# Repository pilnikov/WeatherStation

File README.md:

# WeatherStations

Проект метеостанции на ESP8266/32 (среда - Arduino IDE 1.8.5)

Поддерживаются:

Дисплеи на 7ми и 14ти сегментных индикаторах с драйверами на TM1637, HT16K33, MAX7219 (4/8 Знакомест).

LCD16х2 дисплей со встроеным знакогенератором кириллицы, интерфейс  I2C.

Матричные дисплеи на:
        
        MAX7219 8х32 и 16х32 пикселей.
        отдельном контроллере MEGA2560, 16х32 пикселей, полный цвет, интерфейс HUB75
        в версии ЕСП32, 64х64 пикселей, полный цвет, интерфейс HUB75 
        Holtek HT1632, 16х32 пикселей, 3 цвета (R, G, Orange) от Sure Electronics

Модули RTC на DS1307, DS1302, DS3231.

Управление яркостью дисплеев посредством датчика освещенности ВН1750 или фоторезистора.

Погодные датчики DHT22, Si7021, BME(/P)085/180/280, AM2320, вcтроеный в DS3231 датчик температуры.

Обмен данными между 2мя и более устройствами внутри сети посредством JSON запросов и через облачный сервис ThingSpeak.

Клиент/серверная архитектура.

Возможность работы в режиме "WiFi датчик".

Прогноз погоды с GisMeteo и OpenWeatherMap.

Синхронизация времени с NTP.

6 многофункциональных будильников с 15ю мелодиями.

Настойка через веб интерфейс.

Обновление по OTA, mdns.

Новости с newsapi.

Конфигурирование GPIO.

Дауншифтовая версия на MEGA2560 без возможности перенастройки, без прогноза, без новостей.

Немного мультиков
https://yadi.sk/i/UXBMaSDD3HfCZC

https://yadi.sk/i/Ew0egvWq3Hg48u

https://yadi.sk/i/os1wRLuz3Hg493

https://yadi.sk/i/jCs5TbVB3aA5pw теперь только один мк, безо всяких мег

https://youtu.be/F3vVPQLzyJk версия с новостями, там же есть ссылки на фото платы

Cхемы в папочке extras, там же и инфа для изготовления печатных плат.

Файлы из папки Data необходимо залить на LittleFS плагином (лежат в  папке dop).

По умолчанию первый раз запускается точка доступа с именем  Web_Clock и паролем 12345678 (задается в файле config.json из папки data перед загрузкой в LittleFS строкой  "ap_ssid":"Web_Clock","ap_pass":"12345678").Веб интерфейс будет доступен по адресу 192.168.4.1.

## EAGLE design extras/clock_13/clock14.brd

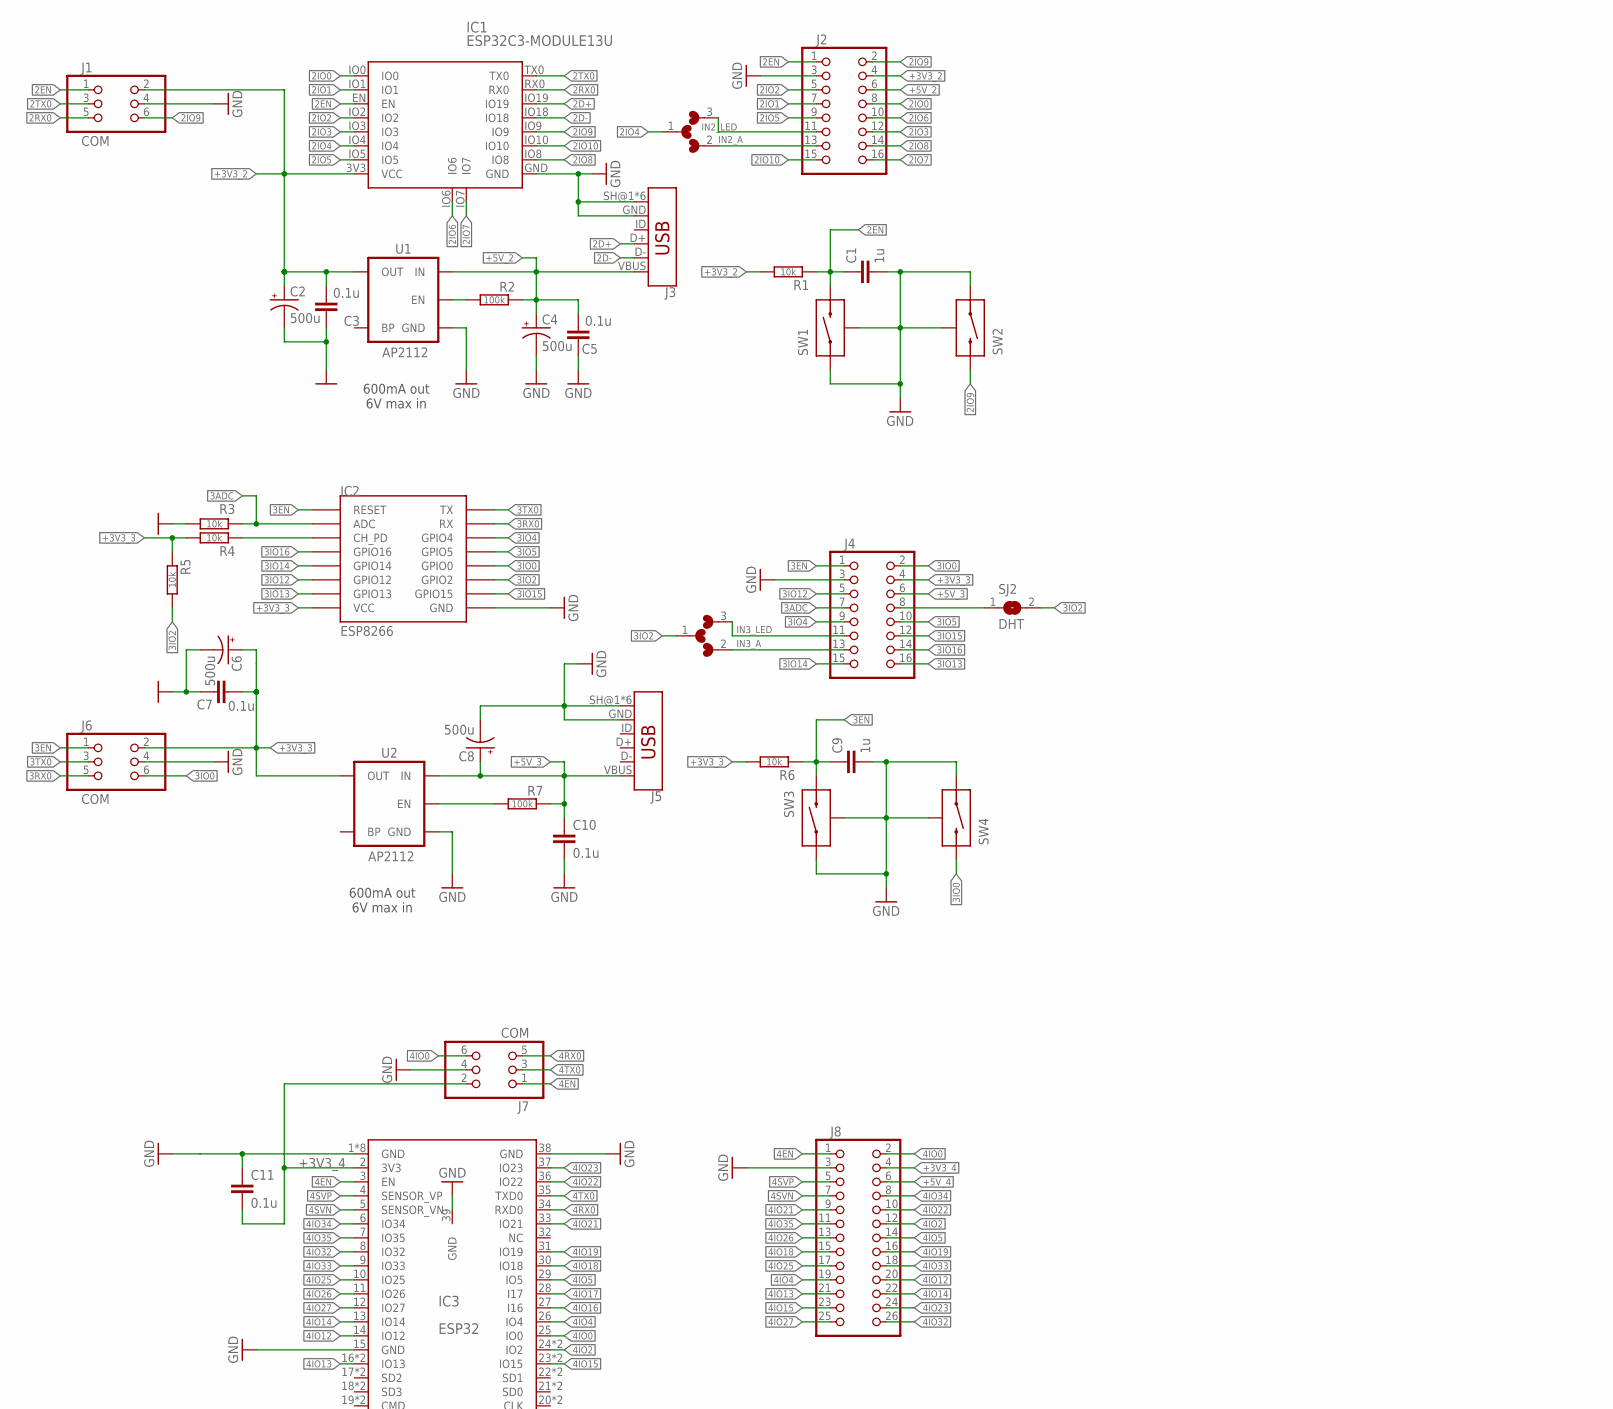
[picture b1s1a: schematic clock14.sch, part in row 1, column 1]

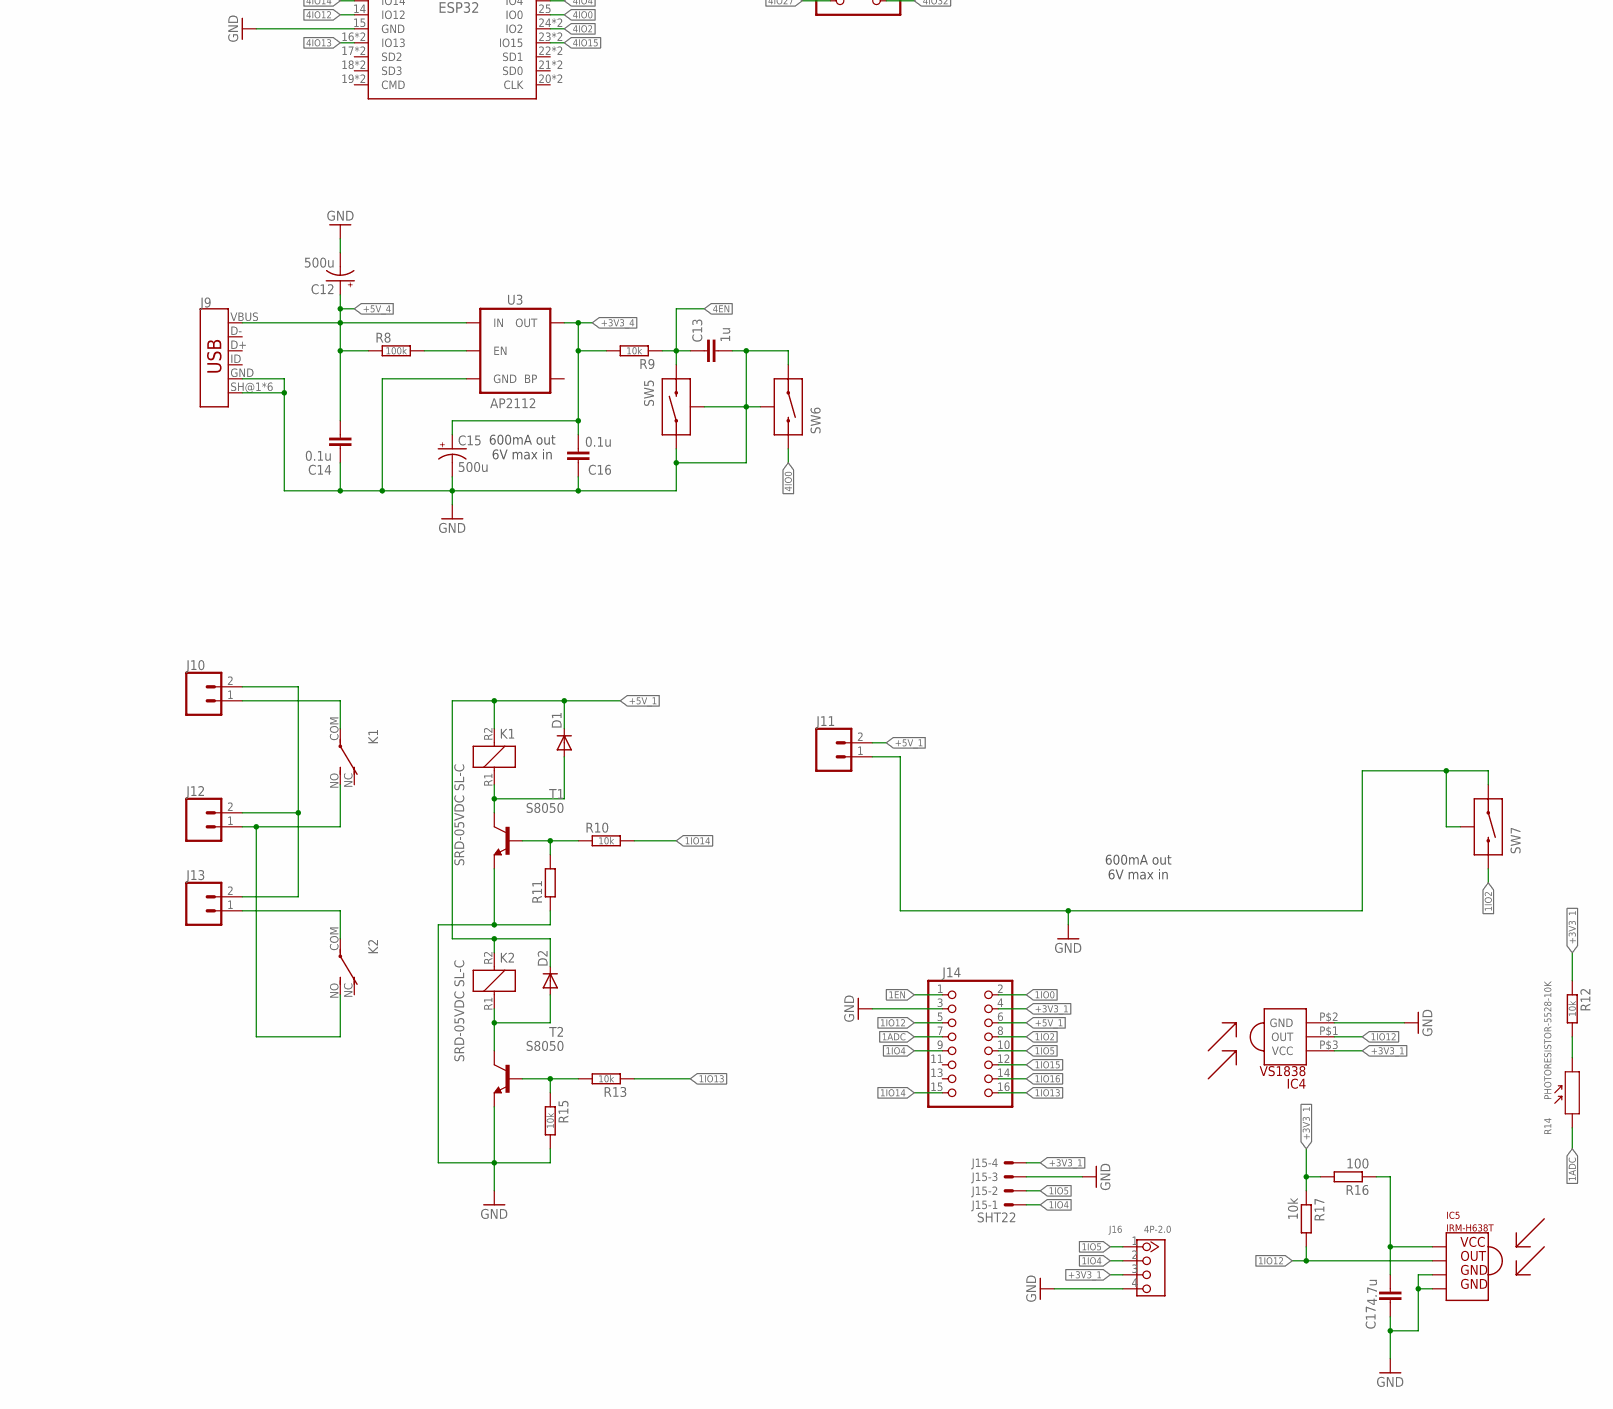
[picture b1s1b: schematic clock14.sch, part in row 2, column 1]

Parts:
C1, C9, C13: 1u; 0603-CAP
C2, C4, C6, C8, C12, C15: 500u; CPOL-RADIAL-100UF-25V
C3, C5, C7, C10, C11, C14, C16: 0.1u; 0603-CAP
C17: 4.7u; 0603-CAP
D1, D2: DIODE-SOD123; SOD123
IC1: ESP32C3-MODULE13U; ESP32C3-13U
IC2: ESP8266; ESP12-SMD
IC3: ESP32; ESP32-WROOVER/WROOM
IC4: VS1838; IR
IC5: IRM-H638T
J1, J6, J7: COM; 2X03_SMT
J2, J4, J14: HEADER-2X8; 2X8
J3, J5, J9: USB_MICRO-BFEMALE_SMT_; USB-B-MICRO-SMD_MY
J8: HEADER-2X13; 2X13
J10, J11, J12, J13: CONN_02; 1X02
J15: SHT22; 70543-04
J16: 4P-2.0; HW4-2.0
K1, K2: SRD-05VDC SL-C; SL-C
R1, R3, R4, R5, R6, R9, R10, R12, R13, R15, R17: 10k; R0603
R2, R7, R8: 100k; R0603
R11: R-EU_R0603; R0603
R14: PHOTORESISTOR-5528-10K; SNR2-3.0
R16: 100; R0603
SJ1, SJ3: L/W; MICROBUILDER_SOLDERJUMPER_ARROW_NOPASTE_3
SJ2: DHT; MICROBUILDER_SOLDERJUMPER_ARROW_NOPASTE
SW1, SW3, SW5: RST; MICROPUSH-BUT_TOP
SW2, SW4, SW6, SW7: PRG; MICROPUSH-BUT_TOP
T1, T2: S8050; SOT23-EBC
U1, U2, U3: AP2112; SOT23-5

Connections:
1ADC: J14.7, R14.1
1EN: J14.1
1EN_P: R8.2, U3.3 (EN)
1IO0: J14.2
1IO2: J14.8, SW7.B
1IO4: J14.9, J15.1, J16.2
1IO5: J14.10, J15.2, J16.1
1IO12: IC4.P$1 (OUT), IC5.OUT, J14.5, R17.2
1IO13: J14.16, R13.1
1IO14: J14.15, R10.2
1IO15: J14.12
1IO16: J14.14
2D+: IC1.IO19, J3.D+
2D-: IC1.IO18, J3.D-
2EN: C1.1, IC1.EN, J1.1, J2.1, R1.1, SW1.B
2EN_P: R2.2, U1.3 (EN)
2IO0: IC1.IO0, J2.8
2IO1: IC1.IO1, J2.7
2IO2: IC1.IO2, J2.5
2IO3: IC1.IO3, J2.12
2IO4: IC1.IO4, SJ1.1
2IO5: IC1.IO5, J2.9
2IO6: IC1.IO6, J2.10
2IO7: IC1.IO7, J2.16
2IO8: IC1.IO8, J2.14
2IO9: IC1.IO9, J1.6, J2.2, SW2.B
2IO10: IC1.IO10, J2.15
2RX0: IC1.RX0, J1.5
2TX0: IC1.TX0, J1.3
3ADC: IC2.ADC, J4.7, R3.1
3EN: C9.1, IC2.RESET, J4.1, J6.1, R6.1, SW3.B
3EN_P: R7.2, U2.3 (EN)
3IO0: IC2.GPIO0, J4.2, J6.6, SW4.B
3IO2: IC2.GPIO2, R5.2, SJ2.2, SJ3.1
3IO4: IC2.GPIO4, J4.9
3IO5: IC2.GPIO5, J4.10
3IO12: IC2.GPIO12, J4.5
3IO13: IC2.GPIO13, J4.16
3IO14: IC2.GPIO14, J4.15
3IO15: IC2.GPIO15, J4.12
3IO16: IC2.GPIO16, J4.14
3RX0: IC2.RXD0 (RX), J6.5
3TX0: IC2.TXD0 (TX), J6.3
4EN: C13.1, IC3.3 (EN), J7.1, J8.1, R9.1, SW5.B
4IO0: IC3.25 (IO0), J7.6, J8.2, SW6.B
4IO2: IC3.24 (IO2), IC3.48 (IO2), J8.12
4IO4: IC3.26 (IO4), J8.19
4IO5: IC3.29 (IO5), J8.14
4IO12: IC3.14 (IO12), J8.20
4IO13: IC3.16 (IO13), IC3.40 (IO13), J8.21
4IO14: IC3.13 (IO14), J8.22
4IO15: IC3.23 (IO15), IC3.47 (IO15), J8.23
4IO16: IC3.27 (I16)
4IO17: IC3.28 (I17)
4IO18: IC3.30 (IO18), J8.15
4IO19: IC3.31 (IO19), J8.16
4IO21: IC3.33 (IO21), J8.9
4IO22: IC3.36 (IO22), J8.10
4IO23: IC3.37 (IO23), J8.24
4IO25: IC3.10 (IO25), J8.17
4IO26: IC3.11 (IO26), J8.13
4IO27: IC3.12 (IO27), J8.25
4IO32: IC3.8 (IO32), J8.26
4IO33: IC3.9 (IO33), J8.18
4IO34: IC3.6 (IO34), J8.8
4IO35: IC3.7 (IO35), J8.11
4RX0: IC3.34 (RXD0), J7.5
4SVN: IC3.5 (SENSOR_VN), J8.7
4SVP: IC3.4 (SENSOR_VP), J8.5
4TX0: IC3.35 (TXD0), J7.3
+3V3_1: IC4.P$3 (VCC), J14.4, J15.4, J16.3, R12.1, R16.2, R17.1
+3V3_2: C2.1 (+), C3.2, IC1.3V3 (VCC), J1.2, J2.4, R1.2, U1.5 (OUT)
+3V3_3: C6.1 (+), C7.2, IC2.VCC, J4.4, J6.2, R4.2, R5.1, R6.2, U2.5 (OUT)
+3V3_4: C11.2, C15.1 (+), C16.2, IC3.2 (3V3), J7.2, J8.4, R9.2, U3.5 (OUT)
+5V_1: D1.C, D2.C, J11.2, J14.6, K1.R2 (2), K2.R2 (2)
+5V_2: C4.1 (+), C5.2, J2.6, J3.VBUS, R2.1, U1.1 (IN)
+5V_3: C8.1 (+), C10.1, J4.6, J5.VBUS, R7.1, U2.1 (IN)
+5V_4: C12.1 (+), C14.1, J8.6, J9.VBUS, R8.1, U3.1 (IN)
GND: C1.2, C2.2 (-), C3.1, C4.2 (-), C5.1, C6.2 (-), C7.1, C8.2 (-), C9.2, C10.2, C11.1, C12.2 (-), C13.2, C14.2, C15.2 (-), C16.1, C17.2, IC1.GND, IC2.GND, IC3.1 (GND), IC3.15 (GND), IC3.38 (GND), IC3.39 (GND), IC3.GND, IC3.PAD$1 (GND), IC3.PAD$4 (GND), IC3.PAD$5 (GND), IC3.PAD$7 (GND), IC3.PAD$8 (GND), IC3.PAD$9 (GND), IC4.P$2 (GND), IC5.GND, IC5.GND1, J1.4, J2.3, J3.GND, J3.SH@1 (SHIELD), J3.SH@2 (SHIELD), J3.SH@3 (SHIELD), J3.SH@4 (SHIELD), J3.SH@5 (SHIELD), J3.SH@6 (SHIELD), J4.3, J5.GND, J5.SH@1 (SHIELD), J5.SH@2 (SHIELD), J5.SH@3 (SHIELD), J5.SH@4 (SHIELD), J5.SH@5 (SHIELD), J5.SH@6 (SHIELD), J6.4, J7.4, J8.3, J9.GND, J9.SH@1 (SHIELD), J9.SH@2 (SHIELD), J9.SH@3 (SHIELD), J9.SH@4 (SHIELD), J9.SH@5 (SHIELD), J9.SH@6 (SHIELD), J11.1, J14.3, J15.3, J16.4, R3.2, R11.1, R15.2, SW1.A, SW1.SH0 (SH), SW2.A, SW2.SH0 (SH), SW3.A, SW3.SH0 (SH), SW4.A, SW4.SH0 (SH), SW5.A, SW5.SH0 (SH), SW6.A, SW6.SH0 (SH), SW7.A, SW7.SH0 (SH), T1.E, T2.E, U1.2 (GND), U2.2 (GND), U3.2 (GND)
IN2_A: J2.13, SJ1.2
IN2_LED: J2.11, SJ1.3
IN3_A: J4.13, SJ3.2
IN3_DHT: J4.8, SJ2.1
IN3_LED: J4.11, SJ3.3
IN_L: J12.1, K1.NO, K2.NO
N: J10.2, J12.2, J13.2
unnamed: IC2.CH_PD, R4.1
unnamed: D1.A, K1.R1 (1), T1.C
unnamed: R10.1, R11.2, T1.B
unnamed: D2.A, K2.R1 (1), T2.C
unnamed: R13.2, R15.1, T2.B
unnamed: R12.2, R14.2
unnamed: C17.1, IC5.VCC, R16.1
OUT_L1: J10.1, K1.COM
OUT_L2: J13.1, K2.COM

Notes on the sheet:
600mA out 6V max in

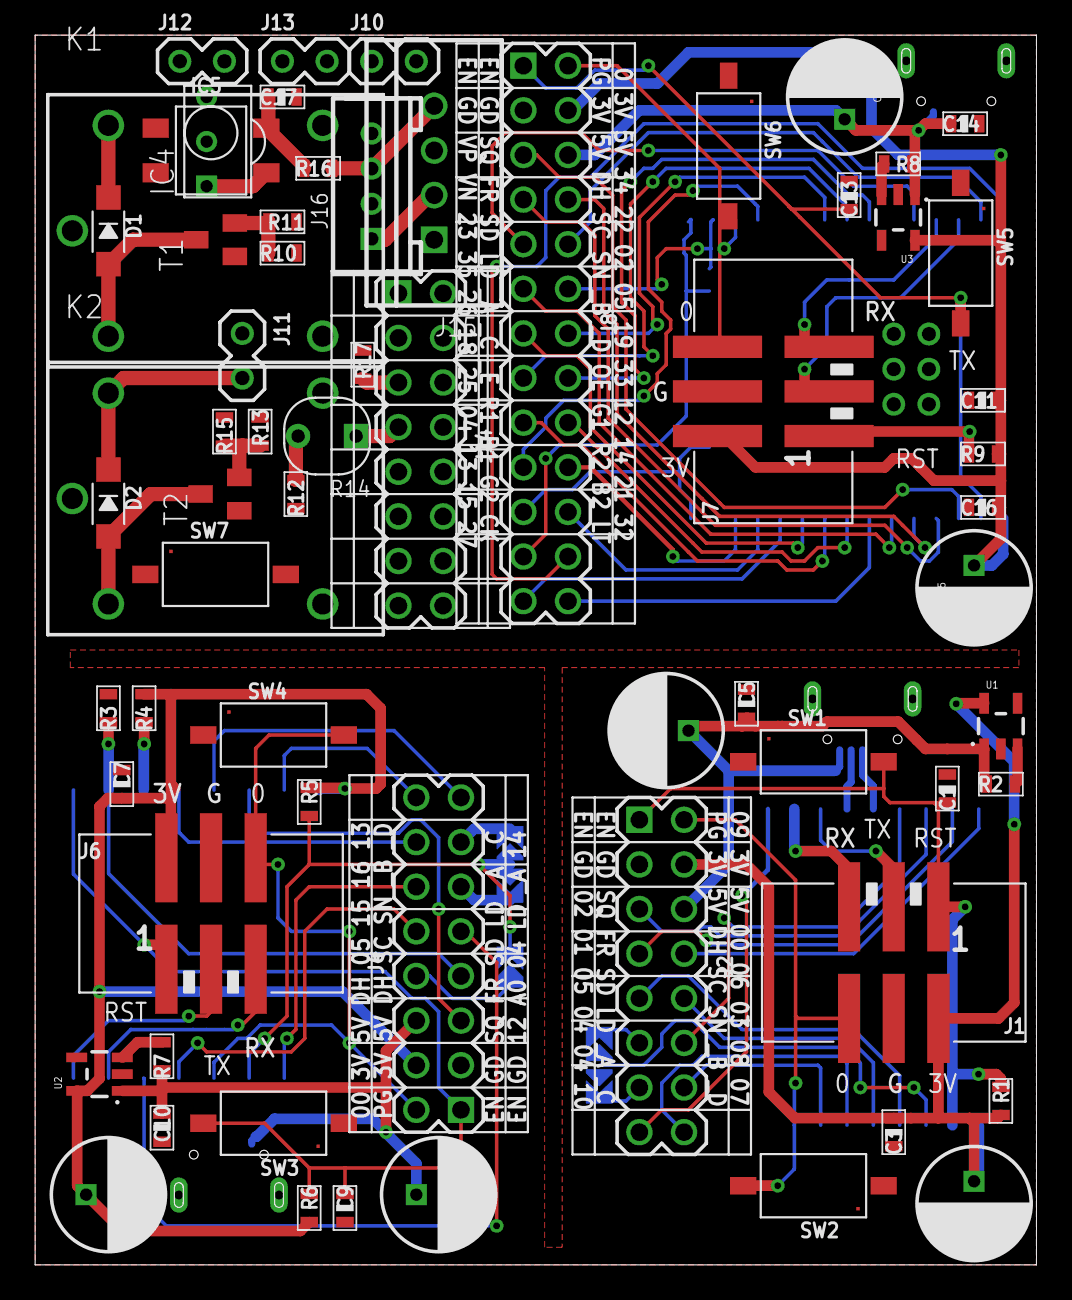
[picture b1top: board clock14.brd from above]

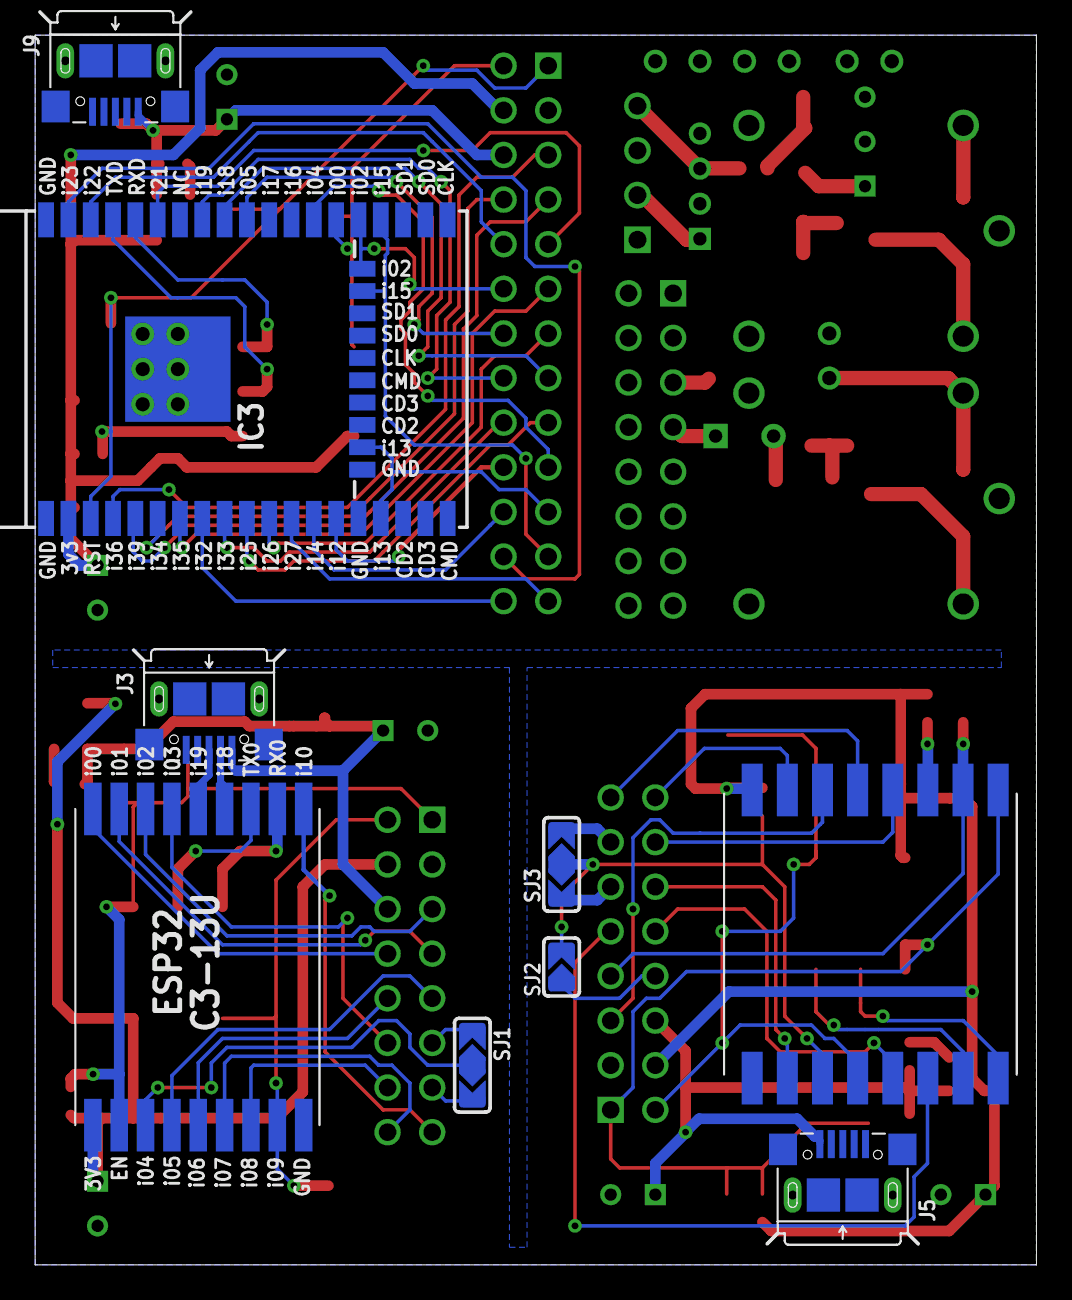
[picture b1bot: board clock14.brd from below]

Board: 2 copper layers, 57.0 x 70.0 mm, 74 parts (9 on the bottom side), 89 nets.

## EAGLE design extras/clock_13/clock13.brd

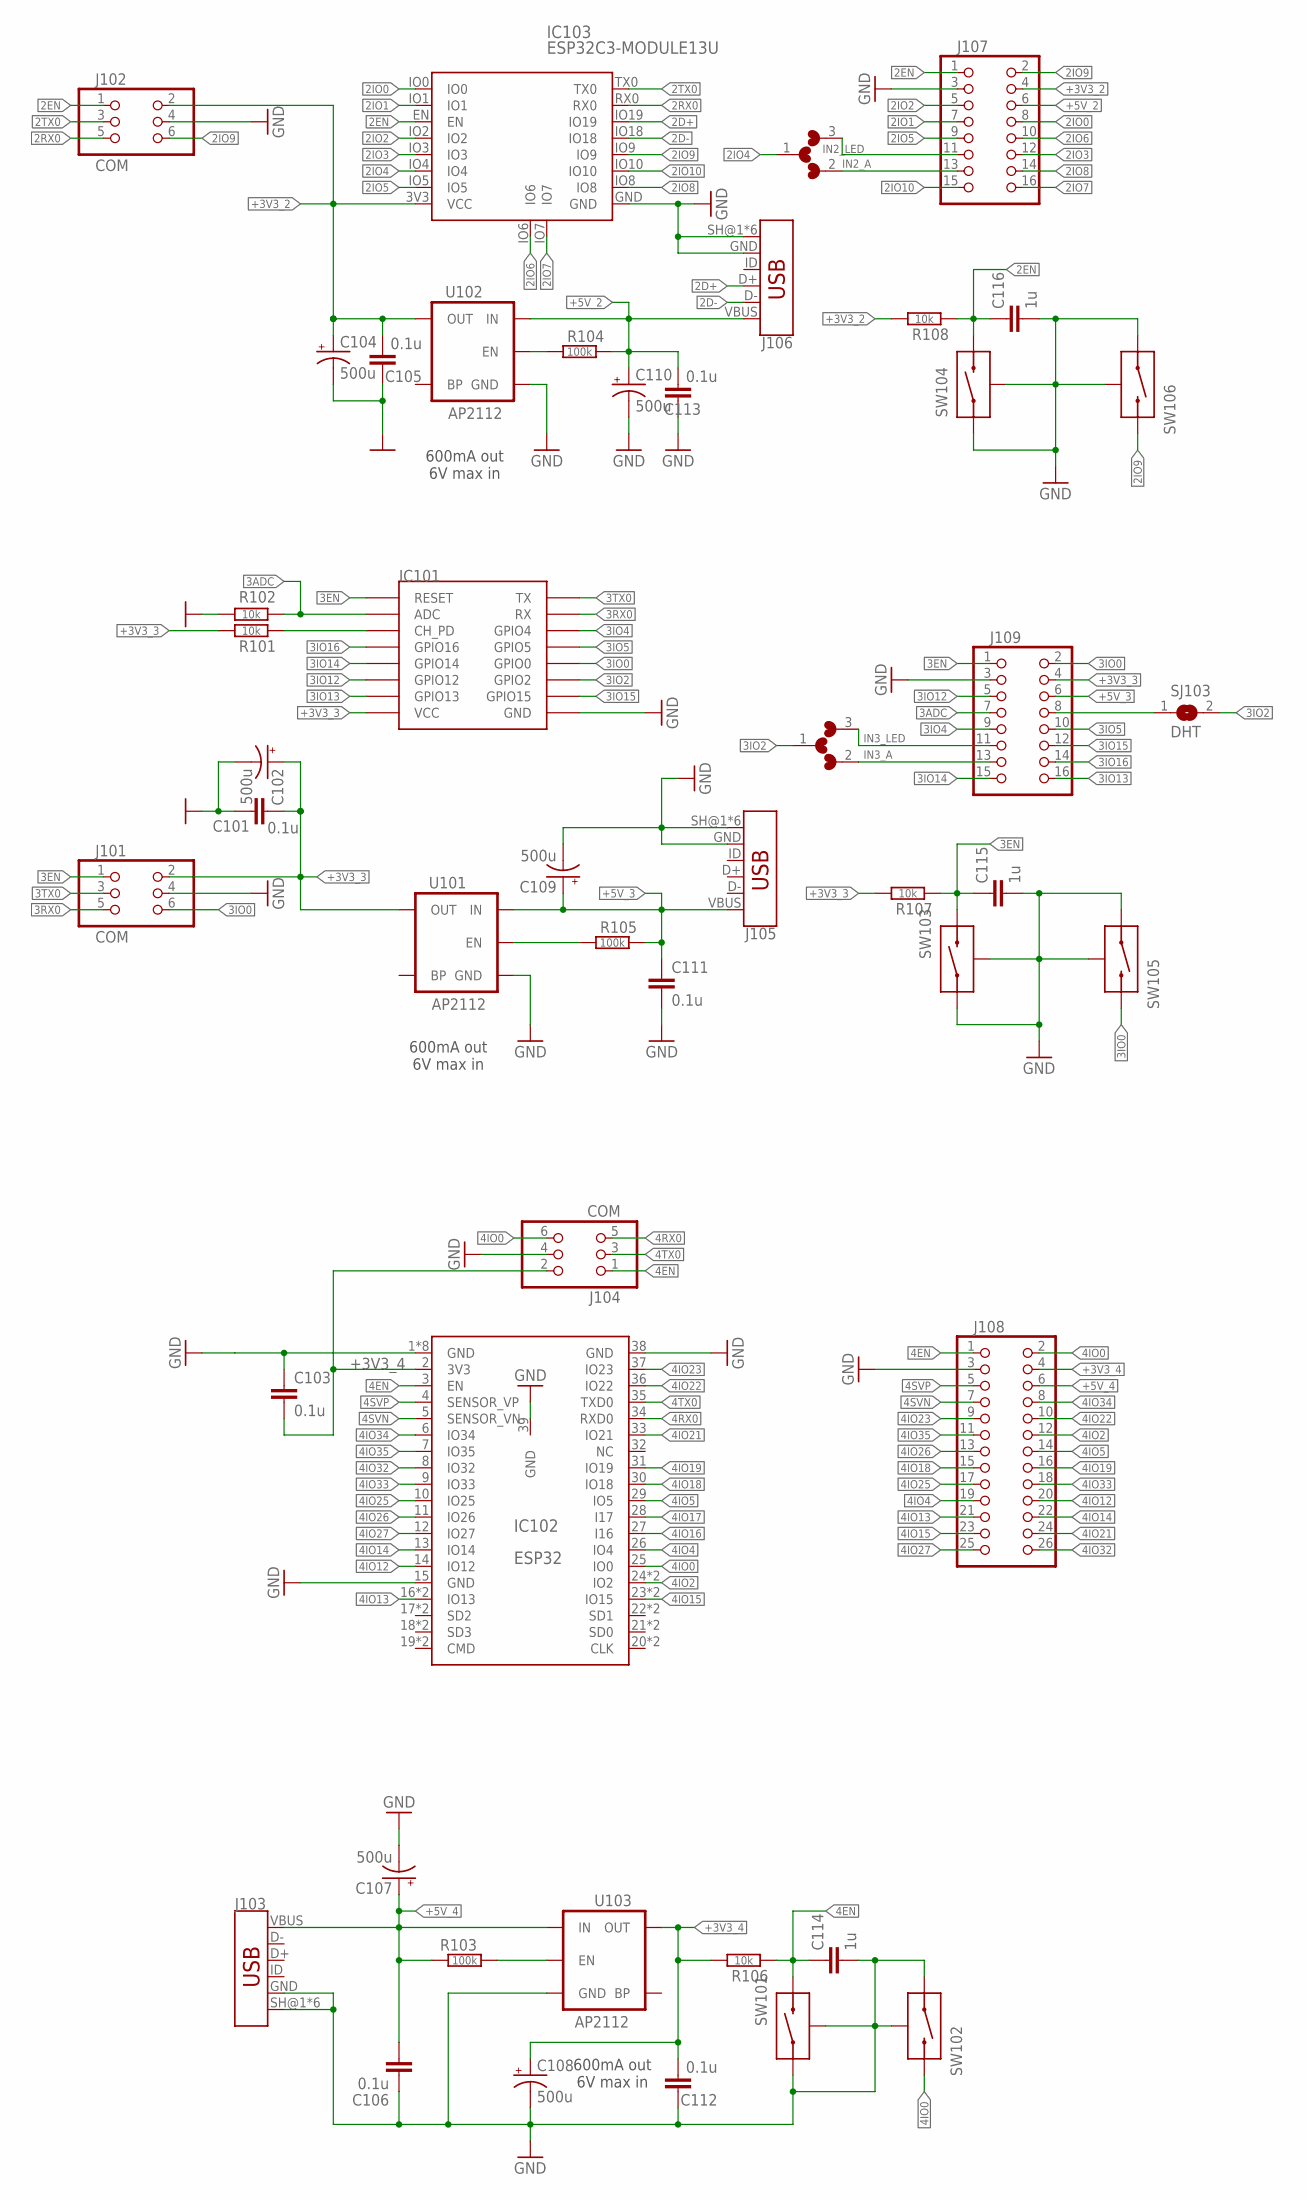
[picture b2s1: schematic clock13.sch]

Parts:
C101, C103, C105, C106, C111, C112, C113: 0.1u; 0603-CAP
C102, C104, C107, C108, C109, C110: 500u; CPOL-RADIAL-100UF-25V
C114, C115, C116: 1u; 0603-CAP
IC101: ESP12SMD; ESP12-SMD
IC102: ESP32; ESP32-WROOVER/WROOM
IC103: ESP32C3-MODULE13U; ESP32C3-13U
J101, J102, J104: COM; 2X03_SMT
J103, J105, J106: USB_MICRO-BFEMALE_SMT_; USB-B-MICRO-SMD_MY
J107, J109: HEADER-2X8; 2X8
J108: HEADER-2X13; 2X13
R101, R102, R106, R107, R108: 10k; R0603
R103, R104, R105: 100k; R0603
SJ101, SJ102: L/W; MICROBUILDER_SOLDERJUMPER_ARROW_NOPASTE_3
SJ103: DHT; MICROBUILDER_SOLDERJUMPER_ARROW_NOPASTE
SW101, SW103, SW104: RST; MICROPUSH-BUT_TOP
SW102, SW105, SW106: PRG; MICROPUSH-BUT_TOP
U101, U102, U103: AP2112; SOT23-5

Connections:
1EN_P: R103.2, U103.3 (EN)
2D+: IC103.IO19, J106.D+
2D-: IC103.IO18, J106.D-
2EN: C116.1, IC103.EN, J102.1, J107.1, R108.1, SW104.B
2EN_P: R104.2, U102.3 (EN)
2IO0: IC103.IO0, J107.8
2IO1: IC103.IO1, J107.7
2IO2: IC103.IO2, J107.5
2IO3: IC103.IO3, J107.12
2IO4: IC103.IO4, SJ101.1
2IO5: IC103.IO5, J107.9
2IO6: IC103.IO6, J107.10
2IO7: IC103.IO7, J107.16
2IO8: IC103.IO8, J107.14
2IO9: IC103.IO9, J102.6, J107.2, SW106.B
2IO10: IC103.IO10, J107.15
2RX0: IC103.RX0, J102.5
2TX0: IC103.TX0, J102.3
3ADC: IC101.ADC, J109.7, R102.1
3EN: C115.1, IC101.RESET, J101.1, J109.1, R107.1, SW103.B
3EN_P: R105.2, U101.3 (EN)
3IO0: IC101.GPIO0, J101.6, J109.2, SW105.B
3IO2: IC101.GPIO2, SJ102.1, SJ103.2
3IO4: IC101.GPIO4, J109.9
3IO5: IC101.GPIO5, J109.10
3IO12: IC101.GPIO12, J109.5
3IO13: IC101.GPIO13, J109.16
3IO14: IC101.GPIO14, J109.15
3IO15: IC101.GPIO15, J109.12
3IO16: IC101.GPIO16, J109.14
3RX0: IC101.RXD0 (RX), J101.5
3TX0: IC101.TXD0 (TX), J101.3
4EN: C114.1, IC102.3 (EN), J104.1, J108.1, R106.1, SW101.B
4IO0: IC102.25 (IO0), J104.6, J108.2, SW102.B
4IO2: IC102.24 (IO2), IC102.48 (IO2), J108.12
4IO4: IC102.26 (IO4), J108.19
4IO5: IC102.29 (IO5), J108.14
4IO12: IC102.14 (IO12), J108.20
4IO13: IC102.16 (IO13), IC102.40 (IO13), J108.21
4IO14: IC102.13 (IO14), J108.22
4IO15: IC102.23 (IO15), IC102.47 (IO15), J108.23
4IO16: IC102.27 (I16)
4IO17: IC102.28 (I17)
4IO18: IC102.30 (IO18), J108.15
4IO19: IC102.31 (IO19), J108.16
4IO21: IC102.33 (IO21), J108.24
4IO22: IC102.36 (IO22), J108.10
4IO23: IC102.37 (IO23), J108.9
4IO25: IC102.10 (IO25), J108.17
4IO26: IC102.11 (IO26), J108.13
4IO27: IC102.12 (IO27), J108.25
4IO32: IC102.8 (IO32), J108.26
4IO33: IC102.9 (IO33), J108.18
4IO34: IC102.6 (IO34), J108.8
4IO35: IC102.7 (IO35), J108.11
4RX0: IC102.34 (RXD0), J104.5
4SVN: IC102.5 (SENSOR_VN), J108.7
4SVP: IC102.4 (SENSOR_VP), J108.5
4TX0: IC102.35 (TXD0), J104.3
+3V3_2: C104.1 (+), C105.2, IC103.3V3 (VCC), J102.2, J107.4, R108.2, U102.5 (OUT)
+3V3_3: C101.2, C102.1 (+), IC101.VCC, J101.2, J109.4, R101.2, R107.2, U101.5 (OUT)
+3V3_4: C103.2, C108.1 (+), C112.2, IC102.2 (3V3), J104.2, J108.4, R106.2, U103.5 (OUT)
+5V_2: C110.1 (+), C113.2, J106.VBUS, J107.6, R104.1, U102.1 (IN)
+5V_3: C109.1 (+), C111.1, J105.VBUS, J109.6, R105.1, U101.1 (IN)
+5V_4: C106.1, C107.1 (+), J103.VBUS, J108.6, R103.1, U103.1 (IN)
GND: C101.1, C102.2 (-), C103.1, C104.2 (-), C105.1, C106.2, C107.2 (-), C108.2 (-), C109.2 (-), C110.2 (-), C111.2, C112.1, C113.1, C114.2, C115.2, C116.2, IC101.GND, IC102.1 (GND), IC102.15 (GND), IC102.38 (GND), IC102.39 (GND), IC102.GND, IC102.PAD$1 (GND), IC102.PAD$4 (GND), IC102.PAD$5 (GND), IC102.PAD$7 (GND), IC102.PAD$8 (GND), IC102.PAD$9 (GND), IC103.GND, J101.4, J102.4, J103.GND, J103.SH@1 (SHIELD), J103.SH@2 (SHIELD), J103.SH@3 (SHIELD), J103.SH@4 (SHIELD), J103.SH@5 (SHIELD), J103.SH@6 (SHIELD), J104.4, J105.GND, J105.SH@1 (SHIELD), J105.SH@2 (SHIELD), J105.SH@3 (SHIELD), J105.SH@4 (SHIELD), J105.SH@5 (SHIELD), J105.SH@6 (SHIELD), J106.GND, J106.SH@1 (SHIELD), J106.SH@2 (SHIELD), J106.SH@3 (SHIELD), J106.SH@4 (SHIELD), J106.SH@5 (SHIELD), J106.SH@6 (SHIELD), J107.3, J108.3, J109.3, R102.2, SW101.A, SW101.SH0 (SH), SW102.A, SW102.SH0 (SH), SW103.A, SW103.SH0 (SH), SW104.A, SW104.SH0 (SH), SW105.A, SW105.SH0 (SH), SW106.A, SW106.SH0 (SH), U101.2 (GND), U102.2 (GND), U103.2 (GND)
IN2_A: J107.13, SJ101.2
IN2_LED: J107.11, SJ101.3
IN3_A: J109.13, SJ102.2
IN3_DHT: J109.8, SJ103.1
IN3_LED: J109.11, SJ102.3
unnamed: IC101.CH_PD, R101.1

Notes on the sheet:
600mA out 6V max in

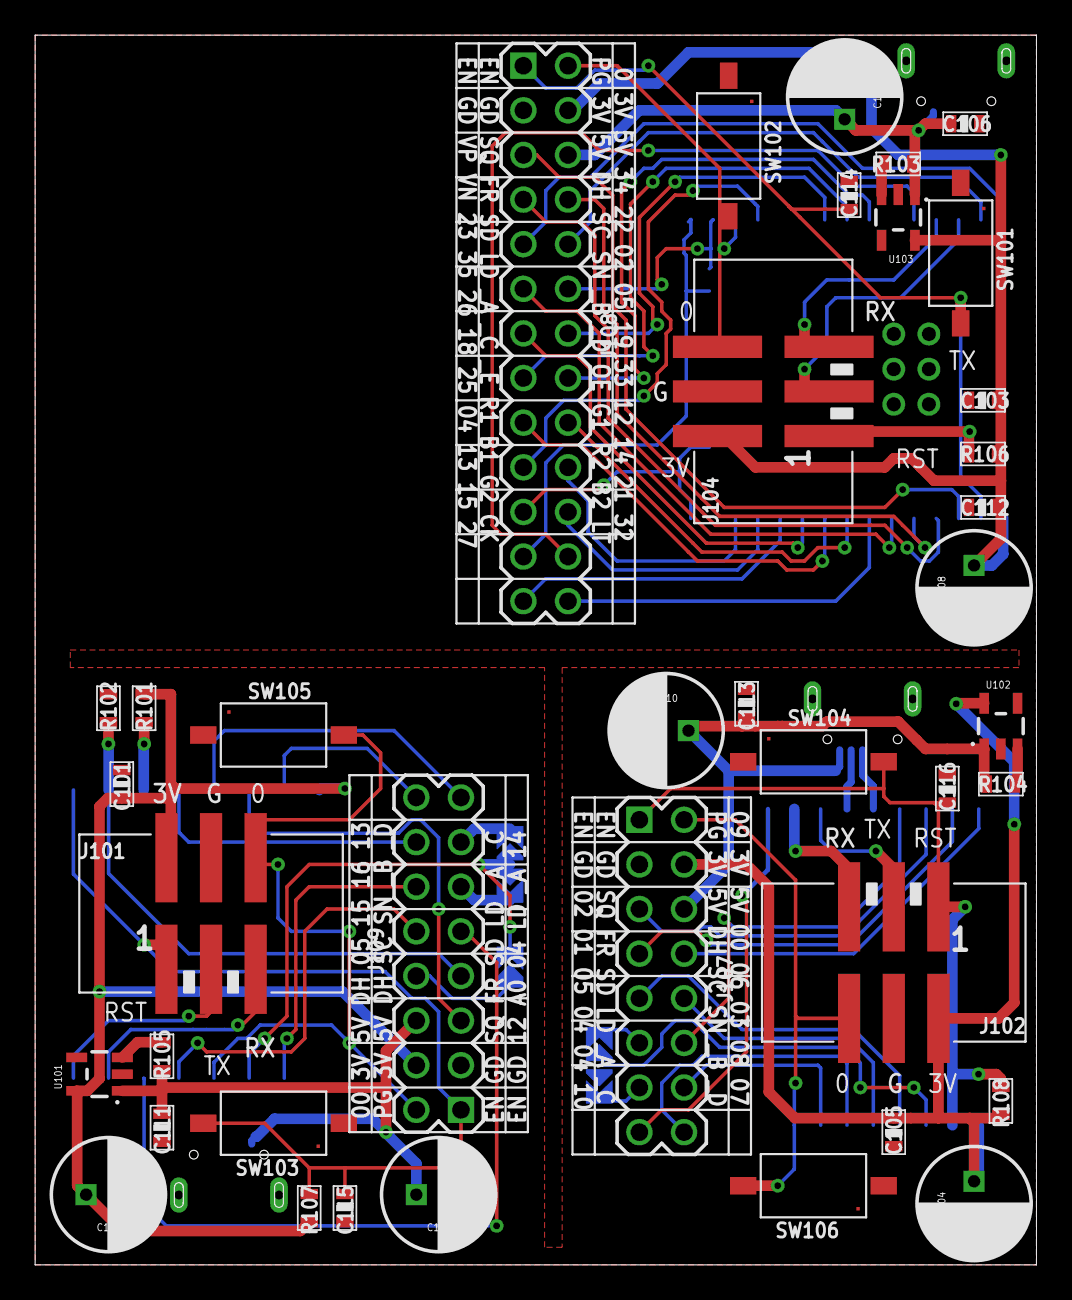
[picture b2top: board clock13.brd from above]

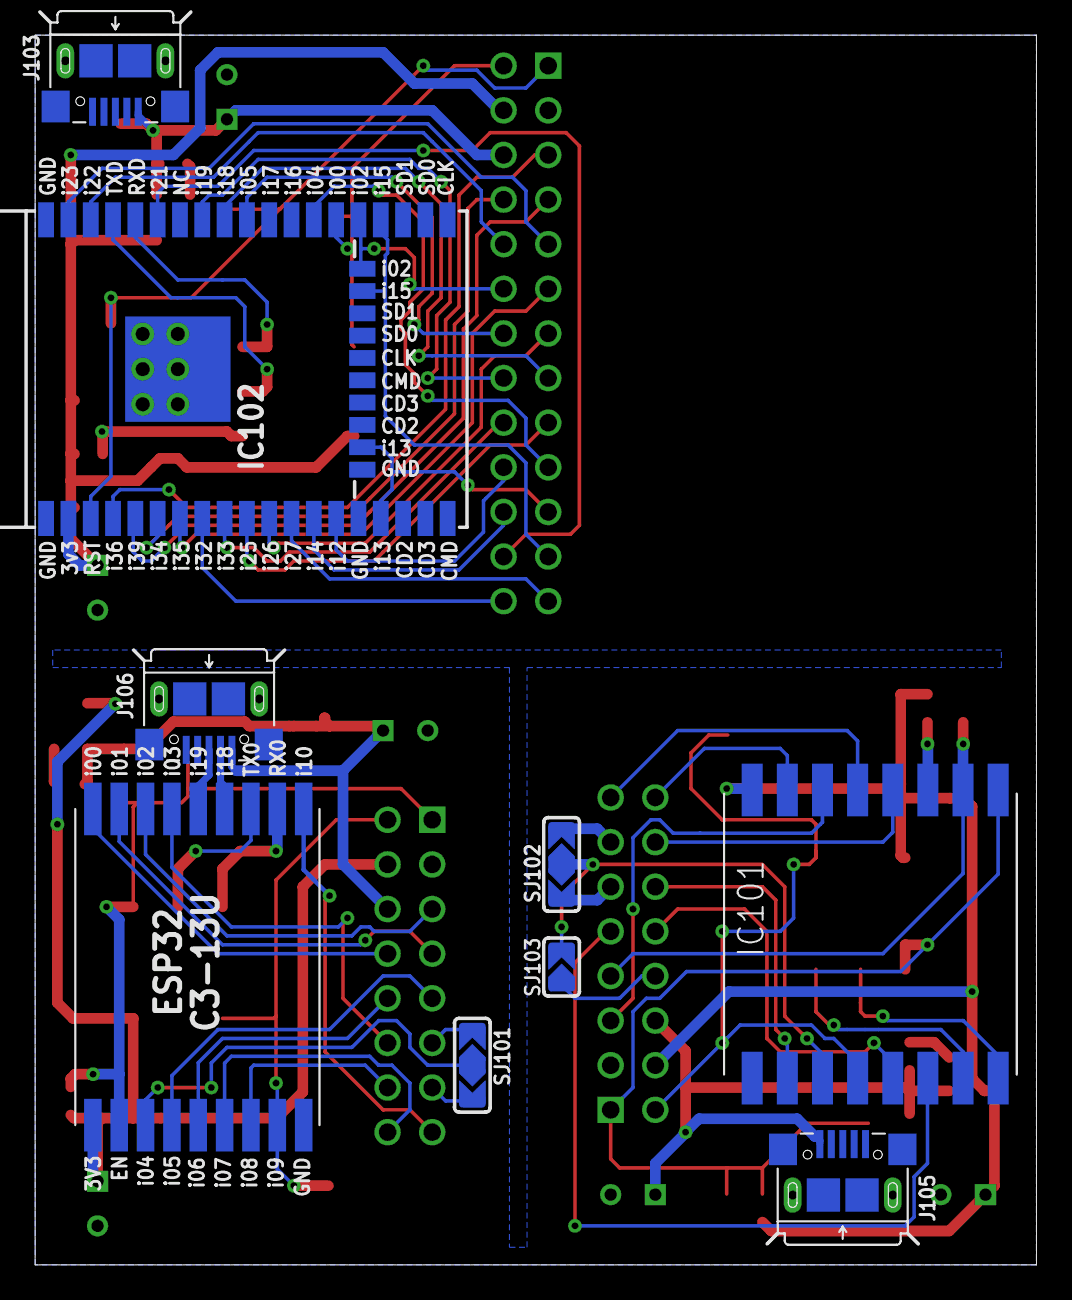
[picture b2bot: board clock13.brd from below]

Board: 2 copper layers, 57.0 x 70.0 mm, 48 parts (9 on the bottom side), 70 nets.

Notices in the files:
parts and their libraries:
SparkFun-PowerIC: Licensing: Creative Commons ShareAlike 4.0 International - https://creativecommons.org/licenses/by-sa/4.0
diy-modules: Released under the Creative Commons Attribution 4.0 International License: http://creativecommons.org/licenses/by/4.0
